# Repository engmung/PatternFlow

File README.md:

<div align="center">

# Patternflow

**An open-source LED synthesizer.**<br />
Play light patterns with your fingertips.

**[Try&nbsp;one&nbsp;in&nbsp;your&nbsp;browser](https://patternflow.work/pattern)** &nbsp;·&nbsp; **[Build&nbsp;one](https://patternflow.work/guide/build)** &nbsp;·&nbsp; **[Get&nbsp;one&nbsp;assembled](https://www.crowdsupply.com/engmung/patternflow)**

</div>

<p align="center">

</p>
<p align="center">
  <sub><a href="https://www.instagram.com/p/DbD2z1VSG09/">▶ the reel: <b>500k+ views</b> on Instagram</a> &nbsp;·&nbsp; <a href="https://youtu.be/1tkV8-AgdpA">▶ <b>the film</b>: the whole story, on YouTube</a></sub>
</p>

> **Photosensitivity warning.** Patternflow displays rapidly changing light patterns that may trigger seizures in people with photosensitive epilepsy. Viewer discretion is advised. If you experience any discomfort, stop use immediately.

**Every Patternflow plays every pattern we make.** Four knobs, and the pattern answers as you turn them: 8,192 points of light, every frame computed live on the device, nothing played back. A pattern is a small file, so one made anywhere plays on all of them. And every part of the instrument is open, from the circuit board to the firmware.

Started by media artist SeungHun Lee ([@engmung](https://github.com/engmung)) in Seoul, and made by everyone who builds one, makes a pattern or sends a fix.

**Start where you are.** [The guide](https://patternflow.work/guide) shows every step on a 3D Patternflow you can turn, in English and Korean, with a **Stuck here?** link on each:

- **[Build](https://patternflow.work/guide/build):** you're soldering one from bare parts, about US$100–200 of them. Or read [BUILD_GUIDE.md](BUILD_GUIDE.md).
- **[Play](https://patternflow.work/guide/play):** yours is built. Flash it, put it on your Wi-Fi, learn the four knobs. Or read [First light](#first-light), below.
- **[Make](https://patternflow.work/guide/make):** make your own patterns, with or without a Patternflow. Or read [PATTERN_GUIDE.md](PATTERN_GUIDE.md).
- **[Audio](https://patternflow.work/guide/audio):** it plays; now add sound and MIDI with the Audio edition. Or read [AUDIO_GUIDE.md](docs/AUDIO_GUIDE.md).

## Where it began

Almost every screen around us is a playback device. It takes in content and shows it to us, and we sit in front of it and watch. Patternflow is different: touch it and it answers in that instant, and nobody plays the same thing twice.

In January 2026 I stopped by the Nam June Paik Art Center, which happened to be running an event marking twenty years since Paik's death. That is how I ended up standing in front of *Participation TV*: you speak into a microphone and the picture on the screen moves with your voice. It turned the viewer from someone watching into someone taking part. I spoke into it, and my voice became the picture.

Two months later I connected an LED matrix and a potentiometer for the first time.

I put my first pattern, *Patternflow: Origin*, on an LED matrix with four knobs and posted it online. Some people asked how to buy it; far more asked how to build it. So everything went public: schematics, firmware, 3D models, the build guide, and the whole workflow for making new patterns.

**A contemporary reinterpretation of Nam June Paik's *Participation TV* (1963). Paik let the audience change the image. Patternflow lets you make it, and give it away.**

## The community responded

<p align="center">
  <sub><i>Builds by Nath (UK), shooter (Poland), day (France), Enerjoy (Norway), SimonePDA (UAE), Nick (USA), and Jon (USA).</i></sub>
</p>

Two of the builds above live in DJ booths. More keep arriving on the **[build map](https://patternflow.work/inside)**: a wooden case in Mexico City, a horizontal desk case in Kyiv that is now one of the remixes in this repo, a plaster shell hanging on a wall in Germany with a Raspberry Pi inside.

I started this alone. It hasn't worked that way for a while now. Web upload began as someone else's suggestion and proof of concept, and shipped as a main feature two days later. The pattern modules that install over Wi-Fi came from **[Simone Majocchi](https://github.com/SimonePDA)**, who designed the loader, built it and proved it on hardware before proposing it. They're core to the instrument now, and Simone went on to bring MQTT, a laser-cut case and the Performance edition. Martin Lopez has put more patterns on the Community wall than anyone, and a Patternflow went to California as thanks.

In Iran, Azmano took Patternflow's patterns, added MIDI and a microphone, and built an instrument of their own that runs in a browser, **[MOTIFLOW](https://azmano.art/portfolio-item/motiflow/)**, shown in a gallery and played at events since. Patternflow had become something people build their own instruments out of.

Underneath is an instrument still being designed, in the open, by whoever shows up. It's already moving in directions I didn't choose, and none of it was assigned. The next one is open too: a bridge for TouchDesigner or Node-RED has a place waiting in [`integrations/`](integrations/README.md), and [Contributing](#contributing) says how to start.

**Patternflow is a thing we're all making now.**

## Make it yours

Try it in the Live Editor, make it in Pattern Lab, share it on Community, and it plays on every Patternflow in the world. Then build one to play it on.

### Patterns

You don't need hardware to start. The **[Live Editor](https://patternflow.work/pattern)** is a Patternflow in your browser: the same knobs, the same detents, no account and no install. Patterns are JavaScript, and you don't have to write it yourself: click **Copy creation prompt**, paste it into your AI assistant with the look you want, paste back the code it returns, and play. The template handles the encoder mapping, brightness curve and pixel buffer; you describe the look.

**[Pattern Lab](https://patternflow.work/pattern-lab)** is the studio, and where a pattern reaches the hardware. Make variations through any AI chat, then shape the color ramps and retune the knob ranges. Send it to your Patternflow and it builds into a small `.pfm` module that installs over Wi-Fi in about ten seconds, with no cable, no reflash and no IDE. Graphic Export renders the same pattern as a print-size PNG for a business card or an MP4 loop for a post, in your browser, with nothing uploaded.

Then publish it to the **[Community](https://community.patternflow.work/community)**: more than a hundred patterns, from quiet waves to chaos-theory studies, all playable under the same four knobs. Collect them into a deck and send it to your board in one click. Browsing needs no account, and publishing asks only a username and password, no email. New studies go up on **[Instagram](https://www.instagram.com/patternflow.work)** almost daily; publish something that stands out and it can get featured there, or ask for a collab and I'll post yours with you. The [Make guide](https://patternflow.work/guide/make) walks the whole loop as a tutorial you do as you read, no hardware needed.

### The device

The **[Build Guide](BUILD_GUIDE.md)** is the official route: the v3.9 board in a 3D-printed case, about US$100–200 in parts ([BOM](BUILD_GUIDE.md#1-bill-of-materials-bom)). Order first and build later: the parts take about two weeks to arrive, and the case prints in about ten hours on a 256 mm bed. The rest is about an hour of hands-on work, half of it soldering, and every joint is a big through-hole one. Every first-timer who has built one finished it, and most came back saying the soldering was the fun part. The **[build guide in 3D](https://patternflow.work/guide/build)** is the same route on a board you can turn.

**Buy the LED panel the [BOM](BUILD_GUIDE.md#off-the-board) links.** It's verified, and the case is measured around its screw holes. Another 128 × 64 panel can match the spec line for line and still stay completely dark, because its driver chips are wrong for the board; **[Panel Compatibility](docs/panel-compatibility.md)** says how to tell before you pay.

Other routes lead to the same instrument. No printer? **[Simone Majocchi's case](hardware/case/remixes/simonepda-lasercut/README.md)** is laser-cut from acrylic or MDF, and [two more printed cases](hardware/case/remixes/README.md) sit beside the official one. No board order? The **[breadboard build](https://patternflow.work/build/breadboard)** wires the same electronics with jumper wires, and that's a real Patternflow, not a temporary prototype. Every other combination is on the **[Assembly Map](docs/assembly/README.md)**. Holding a v2.x board? [BUILD_GUIDE_v2.md](docs/legacy/BUILD_GUIDE_v2.md), with everything it needs bundled at [v2.1.0](https://github.com/engmung/Patternflow/releases/tag/v2.1.0). The current board's known issues and design notes are [BUILD_GUIDE §10](BUILD_GUIDE.md#10-known-issues--design-notes).

**When yours lights up, share it** in [Discord](https://discord.gg/Vr9QtsxeTk) or through the [Share your build](../../issues/new?template=share_build.yml) form, and I'll add your pin to the build map. The goal is simple: cover it with pins.

Rather have one arrive assembled, tested and flashed? It's on **[Crowd Supply](https://www.crowdsupply.com/engmung/patternflow)**, shipped worldwide. The campaign is past its goal and runs until 15 October 2026.

## First light

For a DevKit that has never run Patternflow, or one that needs rescuing. The same steps, with the flasher's own screens and a **Stuck here?** link on each, are the Play guide's **[Flash](https://patternflow.work/guide/play#flash)** and **[Patterns](https://patternflow.work/guide/play#patterns)** chapters; [BUILD_GUIDE §8](BUILD_GUIDE.md#8-firmware) is the same order in writing, with more on each step. Already running Patternflow, or got one assembled? Skip download mode, which erases installed patterns and saved Wi-Fi: power it from `J4` and start at step 5. Later firmware comes from the console's **Update** page over Wi-Fi, which keeps everything.

> **Power goes in through `J4`, the screw terminal, and nowhere else:** a USB cable from a 5 V power bank, cut, red to +5V and black to GND. Never power it through the DevKit's USB-C ports: they are for flashing, with the DevKit out of the board.

1. **Flash the DevKit on its own, out of the board,** from desktop Chrome or Edge. Use its **left** port, labelled `USB` (antenna up, ports toward you): the right one flashes too, but the Wi-Fi step never appears there. Use a USB-C cable that carries data; a charge-only cable is the usual reason nothing shows up.
2. **Download mode first:** hold **BOOT**, tap **RST** (EN on some DevKits), let go of BOOT. Then press **[Flash Patternflow](https://patternflow.work/guide/play#flash-5)**, pick `USB JTAG/serial debug unit` and install. It takes about two minutes and erases the flash, which a new DevKit doesn't mind.
3. **Then the Wi-Fi, which takes a second go.** The dialog usually ends without asking for it, and nothing failed: close it. Press **RST**, press **Flash Patternflow** again and pick the port, and this time it opens on Patternflow's own menu. Choose **Connect to Wi-Fi**, let the short scan finish (it lists nothing, by design), and type your network's exact name (capitals count, 2.4 GHz only) and its password.
4. **Unplug the DevKit from the computer and, with the power bank unplugged, seat it.** Its USB-C ports go toward the `USB` mark on the board, all 44 pins in. Then plug the `J4` cable into the power bank: within a second or two a red, squarish pattern comes on. That's **Origin**, and one pattern is right for now.
5. **Give it 15 seconds, then hold K2, the top-left knob,** for a second. `CONNECTED` and an address: you're on your Wi-Fi. `HOTSPOT` and a name like `patternflow-a1b2`: it found no network it knows, so it became one. Join it (password `patternflow`; the phone will say there's no internet, which is true, and it stays connected), open `http://192.168.4.1/` and add your network on the Wi-Fi page.
6. **Back on that Wi-Fi, install the Basics pack.** On the [decks page](https://community.patternflow.work/community/decks), press **Install to my board** on the Basics card: 33 patterns, no account. The first time, the board asks to format its storage: press **Format storage**, confirm, and the pack installs by itself. The board's console is at `patternflow.local`; on Android, which can't open that name, type the address K2 shows into the card's **Device address** first.

Panel stays dark? Check that the ribbon is in the panel's `IN`, not `OUT`, that red goes to +5V at both `J3` and `J4`, and that the power bank is on; for a panel other than the BOM's, see [Panel Compatibility](docs/panel-compatibility.md). Only starts after a press of RST? See [BUILD_GUIDE §10](BUILD_GUIDE.md#10-known-issues--design-notes). Then finish with [BUILD_GUIDE §9](BUILD_GUIDE.md#9-final-checks): every knob, one power cycle, the back panel, and the knobs last.

## Playing it

Every knob does two jobs. Turn it, or give it a short press, and you move the pattern that's running; what each knob does there is the pattern's own decision, so the same knob feels different on every one. Hold it down and a device function opens instead, and a second long-press closes it.

| Hold | Where | Opens |
| :--- | :--- | :--- |
| **K1** | top right | **Brightness** |
| **K2** | top left | **Network**: the board's address. Type it, or `patternflow.local`, into a browser for the web console, every feature the device has, from a phone too. With no Wi-Fi it shows the name of its own network instead |
| **K3** | bottom right | **Knob numbers**, each knob's number on the panel; the order isn't the one you'd guess |
| **K4** | bottom left | **Patterns**: turn to browse what's installed, stop on one to play it, long-press again to close |

### What's on the device

A new board boots into **Origin**, concentric sine waves sampled by an emergent grid. It is the one pattern compiled into the firmware, the failsafe a board can always boot into. Everything else lives on the board's storage as **`.pfm` modules**, up to 128 of them, installed over Wi-Fi with no reflash. Adding a pattern never costs a firmware update, and a firmware update never touches your patterns, your Wi-Fi or your storage.

The **Basics pack** is 33 patterns at the top of the [decks shelf](https://community.patternflow.work/community/decks), one click and no account; or drop its `.zip` on your board's Patterns page yourself. The [Live Editor](https://patternflow.work/pattern) opens with a library of its own, over forty patterns, each one loadable and remixable in the browser.

## MIDI, OSC, MQTT & audio-react

The default firmware is the instrument and nothing else, which leaves the most memory for your patterns. MIDI, OSC, MQTT and audio-react come in **editions**, other builds of the same firmware, installed in one click from **[the editions page](https://patternflow.work/editions)** the way patterns arrive. Switching, and switching back, keeps your patterns, Wi-Fi networks and settings. [The features page](https://patternflow.work/features) shows each feature with a reel of it, and [`docs/EDITIONS.md`](docs/EDITIONS.md) explains why it's arranged this way and how to build an edition of your own.

| | What it does | Edition | Read |
| :--- | :--- | :--- | :--- |
| **MIDI over Wi-Fi** | The panel is a MIDI port in any DAW (Ableton, Logic, Bitwig); its knobs and buttons map like any controller's (Ctrl-M in Live), and CC and Program Change play it back | Audio | [MIDI in Ableton](docs/midi-ableton.md) · [spec](docs/midi-spec.md) |
| **OSC, both ways** | Knobs, presses and pattern switches stream out to Max, TouchDesigner or Resolume; incoming OSC moves the panel exactly like a hand on the knob | Audio | [spec](docs/osc-spec.md) · [Max for Live bridge](integrations/ableton) |
| **Audio-react** | A browser tab's audio in four bands you shape, or a small microphone soldered to the DevKit; every pattern reacts with no audio code of its own | Audio | [AUDIO_GUIDE.md](docs/AUDIO_GUIDE.md) · [extension](tools/patternflow-audio-extension) |
| **MQTT** | Both ways, on the broker you already run; two panels on one broker follow each other | Performance | [spec](docs/mqtt-spec.md) |
| **HTTP** | Knob state, pattern selection, brightness, status | every firmware | [API](docs/rest-api.md) |

The panel plays its own patterns, not a video feed: nothing streams pixels to it. Your rig plays it the way a hand does, through the knobs.

**Performance**, maintained by **[Simone Majocchi](https://github.com/SimonePDA)**, is for a panel that runs a room: sequences on a timeline (cue lists and the night/wake scheduler), MQTT in every role, the weather mapped onto the knobs, and the clock.

<details>
<summary>More on MIDI, OSC, MQTT and audio-react</summary>

**MIDI, over the network.** RTP-MIDI over Wi-Fi: native on macOS and iOS, one free driver on Windows. The Pattern Lab's Director exports a show as exactly the four CC lanes the knobs answer to ([Director → MIDI](docs/director-midi.md)), so a show can play on the panel from Live's transport. Sensitivity per knob, an absolute or relative mode, and the session that reconnects itself all live on the panel's console.

**OSC.** Play Patternflow as a controller for your set, let your set play the light, or both at once. OSC is the language of Max, TouchDesigner, Resolume and Processing, and it carries more than MIDI can: pattern names, floats, a heartbeat. For Ableton Live Suite there's a ready-made Max for Live bridge in [`integrations/ableton`](integrations/ableton): click Connect, map the four knobs to any Live parameters, done.

**MQTT.** Knob turns and pattern changes publish as they happen, and messages coming the other way move the knobs and switch patterns exactly as a hand on the knob would. It puts the panel on the same bus as the rest of a home or venue, so Home Assistant, Node-RED or a lighting desk can turn its knobs and switch its patterns with nothing Patternflow-specific in the middle. Two boards pointed at the same broker follow each other, which is the short version of why it exists. Point it at a broker on the console's **MQTT** page; a pattern can be addressed by name or by slug. Publishing `1` to `<prefix>/sleep` puts the panel to sleep and `0` wakes it, with the state mirrored on `<prefix>/sleep/state`: enough for a Home Assistant switch, and the one command a panel obeys in either role. Simone's work, along with the browser-side zip unpacking that makes pattern packs install in one click.

**Audio-react.** The Chrome/Edge extension in [`tools/patternflow-audio-extension`](tools/patternflow-audio-extension) captures the current tab's audio, splits it into four bands you shape on a response graph, and sends the levels to the panel over a WebSocket. A pattern reads them as ordinary parameters. The panel can also listen for itself: a $5 PDM microphone on five thin leads runs the same analysis on the device, with no computer involved.

</details>

## Quick facts

| | |
| :--- | :--- |
| **Display** | 128 × 64 HUB75 RGB LED matrix, P2.5 (320 × 160 mm); the driver chips decide which panels work ([compatibility](docs/panel-compatibility.md)) |
| **Brain** | ESP32-S3-DevKitC-1 **N16R8** (16 MB flash, 8 MB PSRAM), plugged into sockets, never soldered · drives the panel itself, no sending card |
| **Board** | v3.9, every soldered part through-hole · KiCad source, Gerbers and schematic in [`hardware/`](hardware/README.md) |
| **Input** | 4× EC11 rotary encoders with push-switch ([controls](#playing-it)) |
| **Power** | 5 V from a USB power bank into **`J4`, the screw terminal**, its only power input · about **4 h per 10,000 mAh** at max brightness ([runtime](#power--runtime)) |
| **Size / weight** | 245 × 325 × 36 mm (9.6 × 12.8 × 1.4 in) · 933 g (2.06 lb) |
| **Firmware** | Arduino-compatible C++, patterns as modules switched at runtime, no reflash |
| **Flashing** | From the browser, once over USB with the DevKit out of the board; after that, patterns and firmware updates arrive over Wi-Fi |
| **Connectivity** | Wi-Fi, an [HTTP API](docs/rest-api.md), and a network of its own when no known one is in reach · MIDI, OSC, MQTT and audio-react in one-click [editions](#midi-osc-mqtt--audio-react) |
| **Build** | ~2 weeks for parts · ~10 h of 3D printing · ~1 h hands-on (≈30 min soldering + ≈30 min assembly, first-build friendly) · US$100–200 in parts ([BOM](BUILD_GUIDE.md#1-bill-of-materials-bom)) |
| **License** | MIT code · CC BY-SA 4.0 hardware, docs and bundled patterns · community patterns licensed by their authors ([License](#license)) |

### Power & runtime

Patternflow runs off any standard USB power bank that fits the case's compartment and can supply a couple of amps at 5 V, wired into `J4`. You don't need a wall adapter, so it stays portable.

<details>
<summary>Measured runtimes, sleep mode, and full-white patterns</summary>

In testing, a 40,000 mAh bank dropped about 13% over 2 hours at **full brightness**, which is roughly **15 hours on a full charge**:

| Power bank | Approx. runtime (max brightness) |
| :--- | :--- |
| 10,000 mAh | ~4 hours |
| 20,000 mAh | ~8 hours |
| 40,000 mAh | ~15 hours |

These were measured with a bright generative pattern at maximum brightness, which is how the device is normally used. Lowering the brightness (long-press K1) extends runtime well beyond these figures.

**Sleep mode** takes it further: the panel goes dark, the HUB75 transfer stops and the board idles, while staying on Wi-Fi so a browser (or MQTT, on the Performance edition) can wake it again. Hold K2 for the NETWORK screen, then turn K1; any knob or button wakes it. The pattern that was running comes back, as it does after a full power cut.

**A pattern that fills the screen with white is a different story.** The same 40,000 mAh bank dropped 9% in 30 minutes: about 26.6 W, or roughly 4.8 A at 5 V, which is above what a typical USB-A port is rated for and enough to make the connector warm (~5.5 hours on that bank). The firmware's total power clamp, on by default, keeps that from happening: it holds the panel to a 2.4 A budget, the high-power USB-A rating, so a white-out frame lands at roughly half brightness instead, while an ordinary bright pattern (~1.9 A) never notices. The budget is `power_budget` on the [`/api/display`](docs/rest-api.md#get-apidisplay) endpoint.

</details>

## How it's built

Patternflow is built around a standalone ESP32-S3 driving a HUB75 RGB LED matrix at low resolution, where each pixel reads as a discrete point of light with its own brightness and color. Four rotary encoders feed firmware written in Arduino-compatible C++ around a modular pattern architecture: each pattern is a self-contained module with its own setup, update and draw routines, while the shared framework handles input, LED rendering, mode transitions and color calibration. I designed the PCB myself; the enclosure is 3D-printed by default, with the community remixes in [`hardware/case/remixes/`](hardware/case/remixes/README.md) beside it. A stainless steel version is still in progress.

A local firmware build (PlatformIO, driven by `firmware/bundles/build.sh`) is only for feature development, or for a panel the stock image can't drive (a different driver profile or module layout, [Panel Compatibility](docs/panel-compatibility.md)). The setup is [`firmware/README.md`](firmware/README.md), and a new feature starts at [FEATURE_GUIDE.md](FEATURE_GUIDE.md). Patterns never need it ([Custom Patterns](firmware/CUSTOM_PATTERNS.md)). The Basics pack is built from the repo's own preset sources and zipped by [`firmware/toolchain/make_pack.py`](firmware/toolchain/make_pack.py).

## Repository & documentation

Folder by folder, and what you want to do → where to start: **[docs/REPOSITORY.md](docs/REPOSITORY.md)**. Every doc is indexed in [`docs/README.md`](docs/README.md).

<details>
<summary>The top-level folders</summary>

| Folder | Contents |
| :--- | :--- |
| `firmware/` | Arduino code for ESP32-S3, the custom pattern template, and the toolchain that builds patterns into `.pfm` modules and packs |
| `hardware/` | Enclosure files and electronics source files (case, PCB, Gerbers, schematic PDF) |
| `web/` | Next.js site (landing, the interactive guide, Live Editor, Pattern Lab, community, browser flasher & build server, journal); the breadboard build guide is a React page here |
| `docs/` | The contracts (HTTP, OSC, MIDI, MQTT, audio WebSocket, show files), how the firmware is put together (`EDITIONS.md`), the assembly map, walk-throughs, records and media |
| `tools/` | Desktop-side helpers, including the audio-react browser extension |
| `integrations/` | Host-software bridges: Ableton Live / Max for Live (OSC knob mapping) |
| `.github/` | Issue and PR templates, and the CI that runs on every pull request (web, every firmware edition, doc links, console pages) |

</details>

**Guide (interactive):** [Start here](https://patternflow.work/guide) · [Build it](https://patternflow.work/guide/build) · [Play it](https://patternflow.work/guide/play) · [Make patterns](https://patternflow.work/guide/make) · [Sound and MIDI](https://patternflow.work/guide/audio), in English and Korean<br />
**Build:** [Build Guide](BUILD_GUIDE.md) · [Assembly Map](docs/assembly/README.md) · [Panel Compatibility](docs/panel-compatibility.md) · [Hardware files](hardware/README.md) · [v2.x board](docs/legacy/BUILD_GUIDE_v2.md)<br />
**Play:** [Pattern Guide](PATTERN_GUIDE.md) · [Custom Patterns](firmware/CUSTOM_PATTERNS.md) · [Audio Guide](docs/AUDIO_GUIDE.md) · [MIDI in Ableton](docs/midi-ableton.md)<br />
**Extend:** [Feature Guide](FEATURE_GUIDE.md) · [Editions](docs/EDITIONS.md) · [Firmware build](firmware/README.md) · [Web architecture](web/ARCHITECTURE.md) · [HTTP API](docs/rest-api.md) · [OSC Spec](docs/osc-spec.md) · [MIDI Spec](docs/midi-spec.md) · [MQTT Spec](docs/mqtt-spec.md) · [Director → MIDI](docs/director-midi.md)<br />
**Project:** [Contributing](CONTRIBUTING.md) · [Support](.github/SUPPORT.md) · [Repository map](docs/REPOSITORY.md) · [Changelog](CHANGELOG.md) · [License Summary](docs/LICENSE-SUMMARY.md) · [Manifesto](docs/manifesto.md)<br />
**Links:** [patternflow.work](https://patternflow.work) · [Community](https://community.patternflow.work/community) · [Crowd Supply](https://www.crowdsupply.com/engmung/patternflow) · [Releases](../../releases) · [Discord](https://discord.gg/Vr9QtsxeTk) · [Instagram](https://www.instagram.com/patternflow.work)

## What's new

**Moving fast.** [v3.12.0 is out](https://github.com/engmung/Patternflow/releases/tag/v3.12.0): a board with Macronix flash keeps its patterns now, and Pattern Lab has text layers. Follow the [changelog](CHANGELOG.md) and the [journal](https://patternflow.work/journal) for what's current.

<details>
<summary>Recent releases in brief</summary>

- **[v3.12.0](https://github.com/engmung/Patternflow/releases/tag/v3.12.0)**: a board whose flash is a Macronix part mounts its pattern storage, where a Format used to not stick (fixed by @didusee). Pattern Lab has text layers, /build lets you pick the case, the community's workshop is gone, and the firmware and the site read their shared numbers from one file. Audio is re-cut on this core as v0.7.1; Performance stays at v0.4.0 until its maintainer re-cuts it.
- **[v3.11.0](https://github.com/engmung/Patternflow/releases/tag/v3.11.0)**: installed patterns run faster. The Basics pack is rebuilt and every one of its 33 patterns runs faster, 1.5 times the frames a second at the median, once the firmware is updated and the pack installed again; a pattern you go back to resumes at once instead of loading again. The console is light and reads as one thing, and the Audio edition's page and browser extension are rebuilt: the page says who has the knobs and saves only what you changed, and the extension holds the knobs through silence. Audio is re-cut on this core as v0.7.0; Performance stays at v0.4.0, on core 3.10.4, until its maintainer re-cuts it.
- **[v3.10.5](https://github.com/engmung/Patternflow/releases/tag/v3.10.5)**: every pattern 2.45 ms a frame faster, and a pattern's code moved to PSRAM, so patterns that were refused for size load and the console has more room while one is running. The panel raises its own Wi-Fi hotspot when it knows no network in reach, a panel that crashed says which pattern it was in and where, a pattern that hangs no longer takes the console down with it, and four requests that could reboot the board cannot any more.
- **[v3.10.4](https://github.com/engmung/Patternflow/releases/tag/v3.10.4)**: the panel films properly on a phone. It refreshes at exactly 300 Hz, the one rate the shutter speeds a phone actually uses (1/50, 1/60, 1/100, 1/30) all divide, so the rolling bands are gone at those; 1/120 and slow motion still band, and [the firmware README](firmware/README.md#refresh-rate-anti-flicker-for-video) says why and what to set.
- **[v3.10.3](https://github.com/engmung/Patternflow/releases/tag/v3.10.3)**: the panel's colours come out right. Bright edges had been growing purple and sky-blue fringes and greys read pink; the cause was in the display driver (which bit plane each brightness window actually lights), and part of it was 3.10.1's own dark-end fix. The planes are exactly binary now, and because the fix is in the driver every installed pattern gets it without a rebuild. Also a [Knobs page](docs/rest-api.md#get-apiknobs-and-post-apiknobs) on the device (which way each encoder counts, set from the browser) and the [features catalogue](https://patternflow.work/features). Both editions were re-cut on that core.
- **[v3.10.2](https://github.com/engmung/Patternflow/releases/tag/v3.10.2)**: a Format that did not take stops reporting success, and a storage that will not mount says why.
- **[v3.10.1](https://github.com/engmung/Patternflow/releases/tag/v3.10.1)**: fixed an upload that could reboot the board, a failed settings write that could make the next boot forget a good pattern, a mic-less Audio panel holding the knobs, and MIDI notes that would not let go.
- **[v3.10.0](https://github.com/engmung/Patternflow/releases/tag/v3.10.0)**: a heavy pattern comes on every time.
- **[v3.9.5](https://github.com/engmung/Patternflow/releases/tag/v3.9.5)**: the web console survives a slow Wi-Fi link and a heavy pattern, and thumbnails sit under the knob.
- **[v3.9.0](https://github.com/engmung/Patternflow/releases/tag/v3.9.0)**: the panel is a MIDI port over Wi-Fi, in the Audio edition.
- **[v3.8.0](https://github.com/engmung/Patternflow/releases/tag/v3.8.0)**: the firmware split into [editions](docs/EDITIONS.md), core, Audio (on-board microphone, OSC, browser and phone audio) and Performance (sequences, MQTT, weather), installable in one click and switchable without losing your patterns.
- **[v3.2.0](https://github.com/engmung/Patternflow/releases/tag/v3.2.0)**: patterns install over Wi-Fi as `.pfm` modules, no reflash.

</details>

## Contributing

Builds, documentation fixes, part sourcing tips, enclosure remixes, firmware features and host-software bridges are all welcome. **[CONTRIBUTING.md](CONTRIBUTING.md)** has one table of where each kind goes and what CI runs on it. Questions and ideas go to the **[Discord](https://discord.gg/Vr9QtsxeTk)**, and **[SUPPORT.md](.github/SUPPORT.md)** says where to ask what. Patterns don't come here: publish them from the Pattern Lab to the Community. Galleries, installations and press: [patternflow.work/contact](https://patternflow.work/contact).

## Story so far

<details>
<summary>From a visit to the Nam June Paik Art Center in January 2026 to two exhibitions in October, month by month</summary>

| When | Milestone |
| :--- | :--- |
| **Jan 2026** | *Patternflow: Origin*, my first work as a new media artist, built around 3D-printed forms and the seed of what became Patternflow · visited the Nam June Paik Art Center |
| **Mar 2026** | The Origin pattern ran on a physical LED matrix with four knobs for the first time |
| **Apr 2026** | Instagram and the Arduino subreddit responded strongly (**150,000+ views and 3,700 upvotes**), and the community asked for the files, not a product, so Patternflow went open source · first PCB fabricated *(sponsored by PCBWay)* · website live |
| **May 2026** | Reached **100 GitHub stars** · the Live Editor and Pattern Lab went live · the first collaborator joined · Crowd Supply agreement |
| **Jun 2026** | Nath in the UK finished the first Patternflow built outside the project, from the published files alone · [Crowd Supply pre-launch page](https://www.crowdsupply.com/engmung/patternflow) live · Instagram passed **1,000 followers** · first community-made pattern shared |
| **Jul 2026** | The v3.0 board, every soldered part through-hole · patterns install over Wi-Fi as modules, Simone Majocchi's design · the Pattern Community opened · featured on Creative Applications Network |
| **Aug 2026** | [Crowd Supply campaign](https://www.crowdsupply.com/engmung/patternflow) launched worldwide · firmware split into [editions](docs/EDITIONS.md) (Audio & Performance) over an unchanged core · press in Mixmag Asia, Synthtopia, AMAZONA.de and MATRIXSYNTH |
| **Sep 2026** | The Crowd Supply campaign met its funding goal · the funded units will be printed and assembled by hand in Korea, on boards from PCBWay · the first Patternflow sold as an artwork · FreeRTOS dual-core network isolation and a faster frame push |
| **Oct 2026** | The Crowd Supply campaign, open until 15 October, reached 200% of its goal · v3.11.0 and the Audio guide · *Anbu*, an exhibition by visually impaired artists at Modu Art Space near Seoul Station, with Patternflow versions of their works to play by hand · Patternflow in *USER EXPERIENCE*, a pop-up gallery in San Francisco |
| **Next** | Deliver every Crowd Supply unit at the highest quality · send Patternflow further out into the world · collaborate with more artists · earn academic recognition |
| **2028** | Grow Patternflow into a self-sustaining community and ecosystem, then move on to the next project |

</details>

Longer write-ups and the full story behind each step live on the **[journal](https://patternflow.work/journal)**: the whole process, written up week by week since April, the thinking and the emotions included, and the parts that went badly too. If you want to know why this project exists and what it costs to keep alive, start there.

### Sponsor

Patternflow's PCB fabrication and 3D-printed enclosure are sponsored by **[PCBWay](https://www.pcbway.com/)**. The first PCB came back clean and on-spec, ordering was straightforward, and the team has been genuinely responsive throughout. That support made these milestones possible.

&nbsp;&nbsp;

<sub><i>The first Patternflow PCB, fabricated by PCBWay, and the enclosure they printed.</i></sub>

## License

Two licenses, in two separate files. A file's SPDX header is the authority where one exists; folders are not license boundaries, and files that cannot carry a header (STL, Gerber, images) take the license the nearest README states. Full breakdown in the **[License Summary](docs/LICENSE-SUMMARY.md)**.

- Code (firmware, web, tools, integrations): **MIT** ([LICENSE-MIT](./LICENSE-MIT))
- Hardware, designs & docs: **CC BY-SA 4.0** ([LICENSE-CC-BY-SA](./LICENSE-CC-BY-SA))
- Bundled patterns (the presets shipped in the firmware and the editor): **CC BY-SA 4.0**, per-file SPDX headers.
- Anything sent *to this repository*: inbound = outbound, MIT for code and CC BY-SA 4.0 for the rest, attribution kept in the file (no CLA). See [CONTRIBUTING.md](CONTRIBUTING.md).
- Patterns published *to the Community*: **licensed by their author**, either **CC BY-SA 4.0** (default) or **CC BY 4.0**; a few older ones keep MIT or CC0, so read the pattern's own header. Both permit commercial use with credit; CC BY-SA additionally requires adaptations to stay under the same license. A fork can never be looser than what it came from, and carries a `Based on:` credit to the original author in its source.

"Patternflow" is a trademark of SeungHun Lee.

*The Patternflow series, by SeungHun Lee: LED Synthesizer (2026) · Origin (2026)*

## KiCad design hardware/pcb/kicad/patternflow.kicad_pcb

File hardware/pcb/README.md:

# Patternflow PCB

Custom board for the Patternflow LED synthesizer — ESP32-S3 DevKit on sockets, four EC11 encoders, HUB75 out, screw-terminal power input. KiCad 10 project.

**Current revision: v3.9** — the USB-C power footprint is gone. v3.0 carried a `USB1` receptacle and its `R1`/`R2` CC pull-downs that had to be left unpopulated after a delayed burnout ([#221](https://github.com/engmung/Patternflow/issues/221)); v3.9 removes them from the board outright, so there is exactly one power input and no way to pick the wrong one. Board outline, mounting holes, and every remaining footprint are unchanged from v3.0 — **the v3 cases fit both boards**. All through-hole, no SMD parts at all; every part is listed by MPN in the [BOM](../bom/).

## Board

| Front | Back |
| :---: | :---: |
|  |  |

- **U1** — ESP32-S3 DevKit (N16R8) on 2× 1×22 female sockets; the DevKit itself is never soldered
- **SW1–SW4** — EC11 rotary encoders, inserted from the **back** (silkscreen reminds you: *encoder facing other side*)
- **J1** — 2×8 box header; the panel's HUB75 ribbon plugs in here
- **Power — J4**: a 2-pin screw terminal on the back, and the board's only power input. Strip a USB cable from any power bank and screw the wires in. (v3.0 also had a USB-C receptacle; it was withdrawn from service after a delayed burnout at a connector pin, [#221](https://github.com/engmung/Patternflow/issues/221), and v3.9 carries no USB-C footprint at all)
- **J3** — +5V out to the LED matrix · **C11** — 1000µF bulk cap for the boot transient

## Schematic

Also available as [`schematic.pdf`](schematic.pdf) (no KiCad required).

## Ordering

The board is listed as a [PCBWay shared project](https://www.pcbway.com/project/shareproject/Patternflow_An_LED_synthesizer_776d796c.html) — ordering there needs no Gerber upload and supports Patternflow development. Any fab works, though: upload [`gerber/patternflow_v3.9_gerber.zip`](gerber/) to the fab of your choice (JLCPCB tends to be the cheapest).

| Gerber | Status |
|---|---|
| `patternflow_v3.9_gerber.zip` | ✅ **Order this** — current. Same board as v3.0 with the USB-C input removed |
| `patternflow_v3.0_gerber.zip` | Previous revision — fabricated, assembled, and verified ([#114](https://github.com/engmung/Patternflow/issues/114)). Fits the same cases; only order it if you specifically want the USB-C footprint, which must stay unpopulated ([#221](https://github.com/engmung/Patternflow/issues/221)) |
| `patternflow_v2.1_gerber.zip` | Legacy — last v2.x board. Only for [v2 builds](https://github.com/engmung/Patternflow/releases/tag/v2.1.0); **does not fit the v3 cases** |
| `patternflow_v1.0_gerber.zip` / `v2.0` | Archived early revisions |
| `gerber/experiment/` | Unverified WIP — never order from here |

## Folder layout

- `kicad/` — editable KiCad 10 source (`patternflow.kicad_pro/sch/pcb` + local footprint/3D libs)
- `gerber/` — fab-ready zips, one per revision
- `images/` — renders + schematic export for this README
- `schematic.pdf` — printable schematic

## Regenerating outputs

After editing the KiCad source (paths relative to `hardware/pcb/`):

```sh
# Gerbers + drill (matches the repo zip convention: 14 files, fab layers only)
kicad-cli pcb export gerbers --no-protel-ext \
  --layers F.Cu,B.Cu,F.Paste,B.Paste,F.Silkscreen,B.Silkscreen,F.Mask,B.Mask,Edge.Cuts \
  -o out/ kicad/patternflow.kicad_pcb
kicad-cli pcb export drill --excellon-separate-th --generate-map --map-format gerberx2 -o out/ kicad/patternflow.kicad_pcb

# Schematic PDF + SVG
kicad-cli sch export pdf -o schematic.pdf kicad/patternflow.kicad_sch
kicad-cli sch export svg -e -o images/ kicad/patternflow.kicad_sch

# Board renders
kicad-cli pcb render --side top    --quality high -w 1600 -h 1200 -o images/board_render_top.png    kicad/patternflow.kicad_pcb
kicad-cli pcb render --side bottom --quality high -w 1600 -h 1200 -o images/board_render_bottom.png kicad/patternflow.kicad_pcb
```

## License

CC-BY-SA 4.0 — see the root [LICENSE-CC-BY-SA](../../LICENSE-CC-BY-SA).

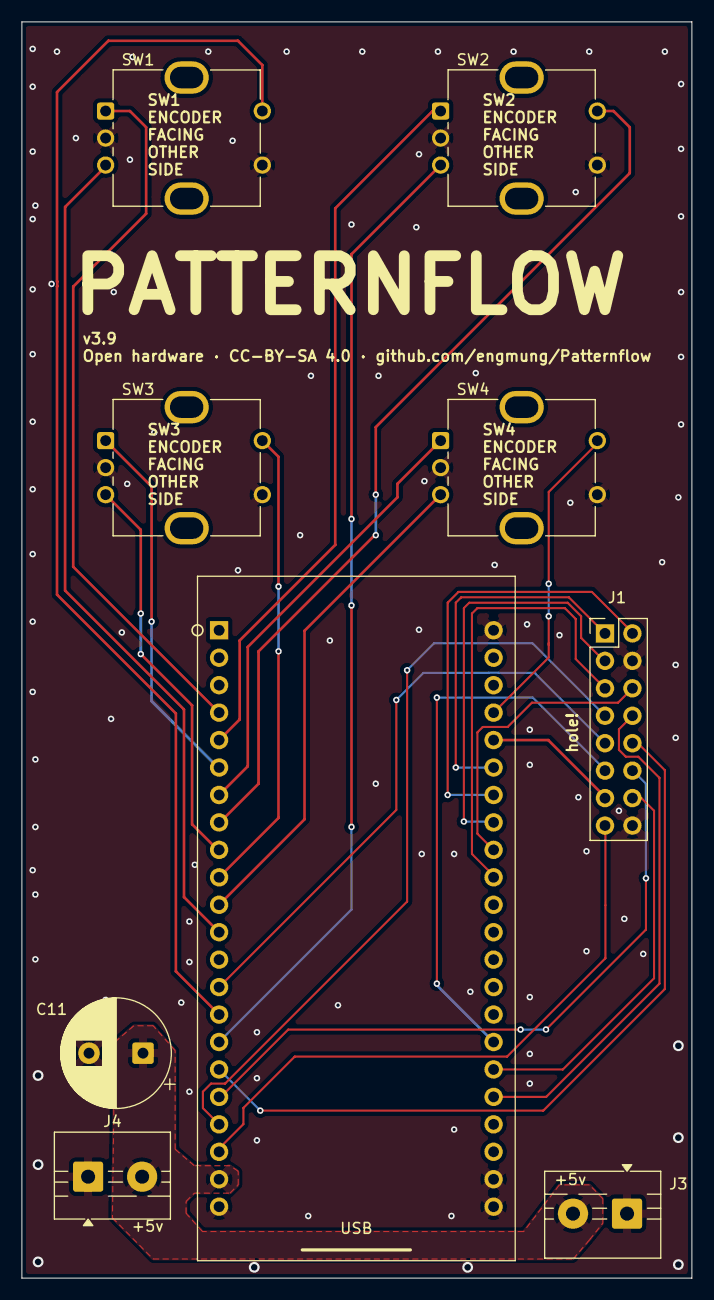
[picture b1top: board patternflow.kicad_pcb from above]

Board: 2 copper layers, 62.0 x 116.2 mm, 9 parts (0 on the bottom side), 28 nets.

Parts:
C11: 1000uF/16V; CP_Radial_D10.0mm_P5.00mm
J1: Conn_02x08_Odd_Even; PinHeader_2x08_P2.54mm_Vertical
J3, J4: Screw_Terminal_01x02; TerminalBlock_MaiXu_MX126-5.0-02P_1x02_P5.00mm
SW1, SW2, SW3, SW4: RotaryEncoder_Switch; RotaryEncoder_Bourns_Vertical_PEC12R-3x17F-Sxxxx
U1: ESP32-S3-DevKit-44pin

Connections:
+5V: C11.1, J3.2, J4.2, U1.21 (5V)
/ENC1_A: SW1.A, U1.4 (IO4)
/ENC1_B: SW1.B, U1.12 (IO8)
/ENC1_SW: SW1.S1, U1.15 (IO9)
/ENC2_A: SW2.A, U1.5 (IO5)
/ENC2_B: SW2.B, U1.16 (IO10)
/ENC2_SW: SW2.S1, U1.8 (IO15)
/ENC3_A: SW3.A, U1.6 (IO6)
/ENC3_B: SW3.B, U1.9 (IO16)
/ENC3_SW: SW3.S1, U1.10 (IO17)
/ENC4_A: SW4.A, U1.7 (IO7)
/ENC4_B: SW4.B, U1.11 (IO18)
/ENC4_SW: SW4.S1, U1.26 (IO1)
/HUB_A: J1.9, U1.14 (IO46)
/HUB_B: J1.10, U1.17 (IO11)
/HUB_B1: J1.3, U1.30 (IO40)
/HUB_B2: J1.7, U1.19 (IO13)
/HUB_C: J1.11, U1.38 (IO48)
/HUB_CLK: J1.13, U1.27 (IO2)
/HUB_D: J1.12, U1.18 (IO12)
/HUB_E: J1.8, U1.40 (IO21)
/HUB_G1: J1.2, U1.29 (IO41)
/HUB_G2: J1.6, U1.31 (IO39)
/HUB_LAT: J1.14, U1.39 (IO47)
/HUB_OE: J1.15, U1.20 (IO14)
/HUB_R1: J1.1, U1.28 (IO42)
/HUB_R2: J1.5, U1.32 (IO38)
GND: C11.2, J1.4, J1.16, J3.1, J4.1, SW1.C, SW1.S2, SW2.C, SW2.S2, SW3.C, SW3.S2, SW4.C, SW4.S2, U1.22 (GND), U1.23 (GND), U1.43 (GND), U1.44 (GND)

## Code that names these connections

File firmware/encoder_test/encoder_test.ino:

// Patternflow - Rotary encoder serial test (standalone diagnostic)
//
// Prints the 4 rotary encoders' click counts and the 4 push-switch states
// over serial. No display / Wi-Fi / audio / patterns — a pure input test
// to check the PCB and wiring.
//
// How to use:
//   1. Open this folder's sketch in Arduino IDE and Upload (same board
//      settings as the main firmware).
//   2. Open Serial Monitor @ 115200.
//   3. Turn a knob  -> its Kn count changes (±1 per detent).
//      Press a knob -> its SW shows DOWN, release -> up.
//
// Reading the result:
//   - A count that moves on its own (untouched)        -> encoder A/B fault
//   - A switch that reads DOWN while untouched          -> switch short/cold joint
//   - Turning/pressing does nothing                     -> open / not connected
//   - Direction reversed: flip INVERT_ENCODER below.
//
// Pins mirror firmware/patternflow/config.h.

#include <Arduino.h>

// --- Encoder + switch pins (match config.h) ---
#define ENC1_A 4
#define ENC1_B 8
#define ENC1_SW 9
#define ENC2_A 5
#define ENC2_B 10
#define ENC2_SW 15
#define ENC3_A 6
#define ENC3_B 16
#define ENC3_SW 17
#define ENC4_A 7
#define ENC4_B 18
#define ENC4_SW 1

#define INVERT_ENCODER 0   // matches main firmware; flip if direction is wrong

const int ENC_A[4]  = { ENC1_A, ENC2_A, ENC3_A, ENC4_A };
const int ENC_B[4]  = { ENC1_B, ENC2_B, ENC3_B, ENC4_B };
const int ENC_SW[4] = { ENC1_SW, ENC2_SW, ENC3_SW, ENC4_SW };

volatile long encPos[4]      = { 0, 0, 0, 0 };
volatile uint8_t encState[4] = { 0, 0, 0, 0 };

// Quadrature decode (same state machine as the main firmware's core_encoders).
static inline void IRAM_ATTR handleEncoder(int idx) {
  uint8_t s = (digitalRead(ENC_A[idx]) << 1) | digitalRead(ENC_B[idx]);
  uint8_t combined = (encState[idx] << 2) | s;
  switch (combined) {
    case 0b0001: case 0b0111: case 0b1110: case 0b1000:
#if INVERT_ENCODER
      encPos[idx]--;
#else
      encPos[idx]++;
#endif
      break;
    case 0b0010: case 0b1011: case 0b1101: case 0b0100:
#if INVERT_ENCODER
      encPos[idx]++;
#else
      encPos[idx]--;
#endif
      break;
  }
  encState[idx] = s;
}

void IRAM_ATTR isr0() { handleEncoder(0); }
void IRAM_ATTR isr1() { handleEncoder(1); }
void IRAM_ATTR isr2() { handleEncoder(2); }
void IRAM_ATTR isr3() { handleEncoder(3); }
void (*const ISRS[4])() = { isr0, isr1, isr2, isr3 };

long getClicks(int idx) { return encPos[idx] / 4; }  // 4 quadrature steps/detent

long lastClicks[4] = { 0, 0, 0, 0 };
int  lastSw[4]     = { HIGH, HIGH, HIGH, HIGH };

void printAll() {
  Serial.print("ENC  ");
  for (int i = 0; i < 4; i++) {
    Serial.printf("K%d=%-4ld %s   ", i + 1, getClicks(i),
                  digitalRead(ENC_SW[i]) == LOW ? "[DOWN]" : "[ up ]");
  }
  Serial.println();
}

void setup() {
  Serial.begin(115200);
  delay(500);
  Serial.println("\n=== Rotary Encoder Test ===");
  Serial.println("Turn a knob -> Kn count changes. Press -> [DOWN].");
  Serial.println("Nothing should change while you are not touching it.\n");

  for (int i = 0; i < 4; i++) {
    pinMode(ENC_A[i], INPUT_PULLUP);
    pinMode(ENC_B[i], INPUT_PULLUP);
    pinMode(ENC_SW[i], INPUT_PULLUP);
    encState[i] = (digitalRead(ENC_A[i]) << 1) | digitalRead(ENC_B[i]);
    lastSw[i] = digitalRead(ENC_SW[i]);
  }
  for (int i = 0; i < 4; i++) {
    attachInterrupt(ENC_A[i], ISRS[i], CHANGE);
    attachInterrupt(ENC_B[i], ISRS[i], CHANGE);
  }

  printAll();  // baseline
}

void loop() {
  bool changed = false;
  for (int i = 0; i < 4; i++) {
    long c = getClicks(i);
    if (c != lastClicks[i]) { lastClicks[i] = c; changed = true; }
    int sw = digitalRead(ENC_SW[i]);
    if (sw != lastSw[i]) { lastSw[i] = sw; changed = true; }
  }
  if (changed) printAll();
  delay(5);
}

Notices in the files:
hardware/pcb/kicad/patternflow.kicad_pcb:
Open hardware · CC-BY-SA 4.0 · github.com/engmung/Patternflow
